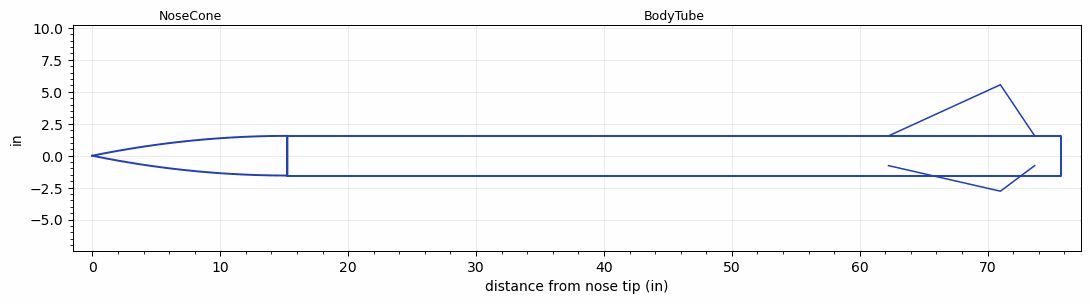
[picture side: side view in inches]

<RASAeroDocument>
 <FileVersion>2</FileVersion>
 <RocketDesign>
  <NoseCone>
   <Length>15.25</Length>
   <Diameter>3.1</Diameter>
   <Shape>Tangent Ogive</Shape>
   <Location>0</Location>
  </NoseCone>
  <BodyTube>
   <Length>60.5</Length>
   <Diameter>3.1</Diameter>
   <RailGuideDiameter>0.5</RailGuideDiameter>
   <RailGuideHeight>0.5</RailGuideHeight>
   <Location>15.25</Location>
   <Fin>
    <Count>3</Count>
    <Chord>11.43</Chord>
    <Span>4</Span>
    <SweepDistance>8.75</SweepDistance>
    <TipChord>0</TipChord>
    <Thickness>0.0625</Thickness>
    <Location>13.5</Location>
    <AirfoilSection>Rounded</AirfoilSection>
    <FX1>1</FX1>
    <FX3>0.5</FX3>
   </Fin>
  </BodyTube>
  <Surface>Smooth (Zero Roughness)</Surface>
  <ModifiedBarrowman>False</ModifiedBarrowman>
  <Turbulence>False</Turbulence>
  <UseBooster1>False</UseBooster1>
  <UseBooster2>False</UseBooster2>
  <Comments>Thunder and Lightning
David Cooper

LDRS-26
Jean Dry Lake

MissleWorks Altimeter
Barometric Altitude = 3577 ft

RASAero II Prediction = 3989 ft
Error = 11.52%
</Comments>
 </RocketDesign>
 <LaunchSite>
  <Altitude>2750</Altitude>
  <Pressure>0</Pressure>
  <RodAngle>0</RodAngle>
  <RodLength>10</RodLength>
  <Temperature>100</Temperature>
  <WindSpeed>0</WindSpeed>
 </LaunchSite>
 <Recovery>
  <Altitude1>1000</Altitude1>
  <Altitude2>1000</Altitude2>
  <Event1>False</Event1>
  <Event2>False</Event2>
  <Size1>1</Size1>
  <Size2>1</Size2>
  <EventType1>None</EventType1>
  <CD1>1.33</CD1>
  <CD2>1.33</CD2>
 </Recovery>
 <SimulationList>
  <Simulation>
   <SustainerEngine>I284W  (AT)</SustainerEngine>
   <SustainerLaunchWt>6.17</SustainerLaunchWt>
   <SustainerCG>51.5</SustainerCG>
   <SustainerIgnitionDelay>0</SustainerIgnitionDelay>
   <Booster1SeparationDelay>0</Booster1SeparationDelay>
   <Booster1IgnitionDelay>0</Booster1IgnitionDelay>
   <IncludeBooster1>False</IncludeBooster1>
   <Booster2Delay>0</Booster2Delay>
   <IncludeBooster2>False</IncludeBooster2>
   <TimetoApogee>14.82024</TimetoApogee>
   <MaxAltitude>3989.283</MaxAltitude>
   <MaxVelocity>632.0986</MaxVelocity>
  </Simulation>
 </SimulationList>
</RASAeroDocument>
